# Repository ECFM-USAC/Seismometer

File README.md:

# Seismometer
Seismometer based on a high sensitivity geophone developed with a 24-bit delta-sigma ADC and ESP32 microcontroller.

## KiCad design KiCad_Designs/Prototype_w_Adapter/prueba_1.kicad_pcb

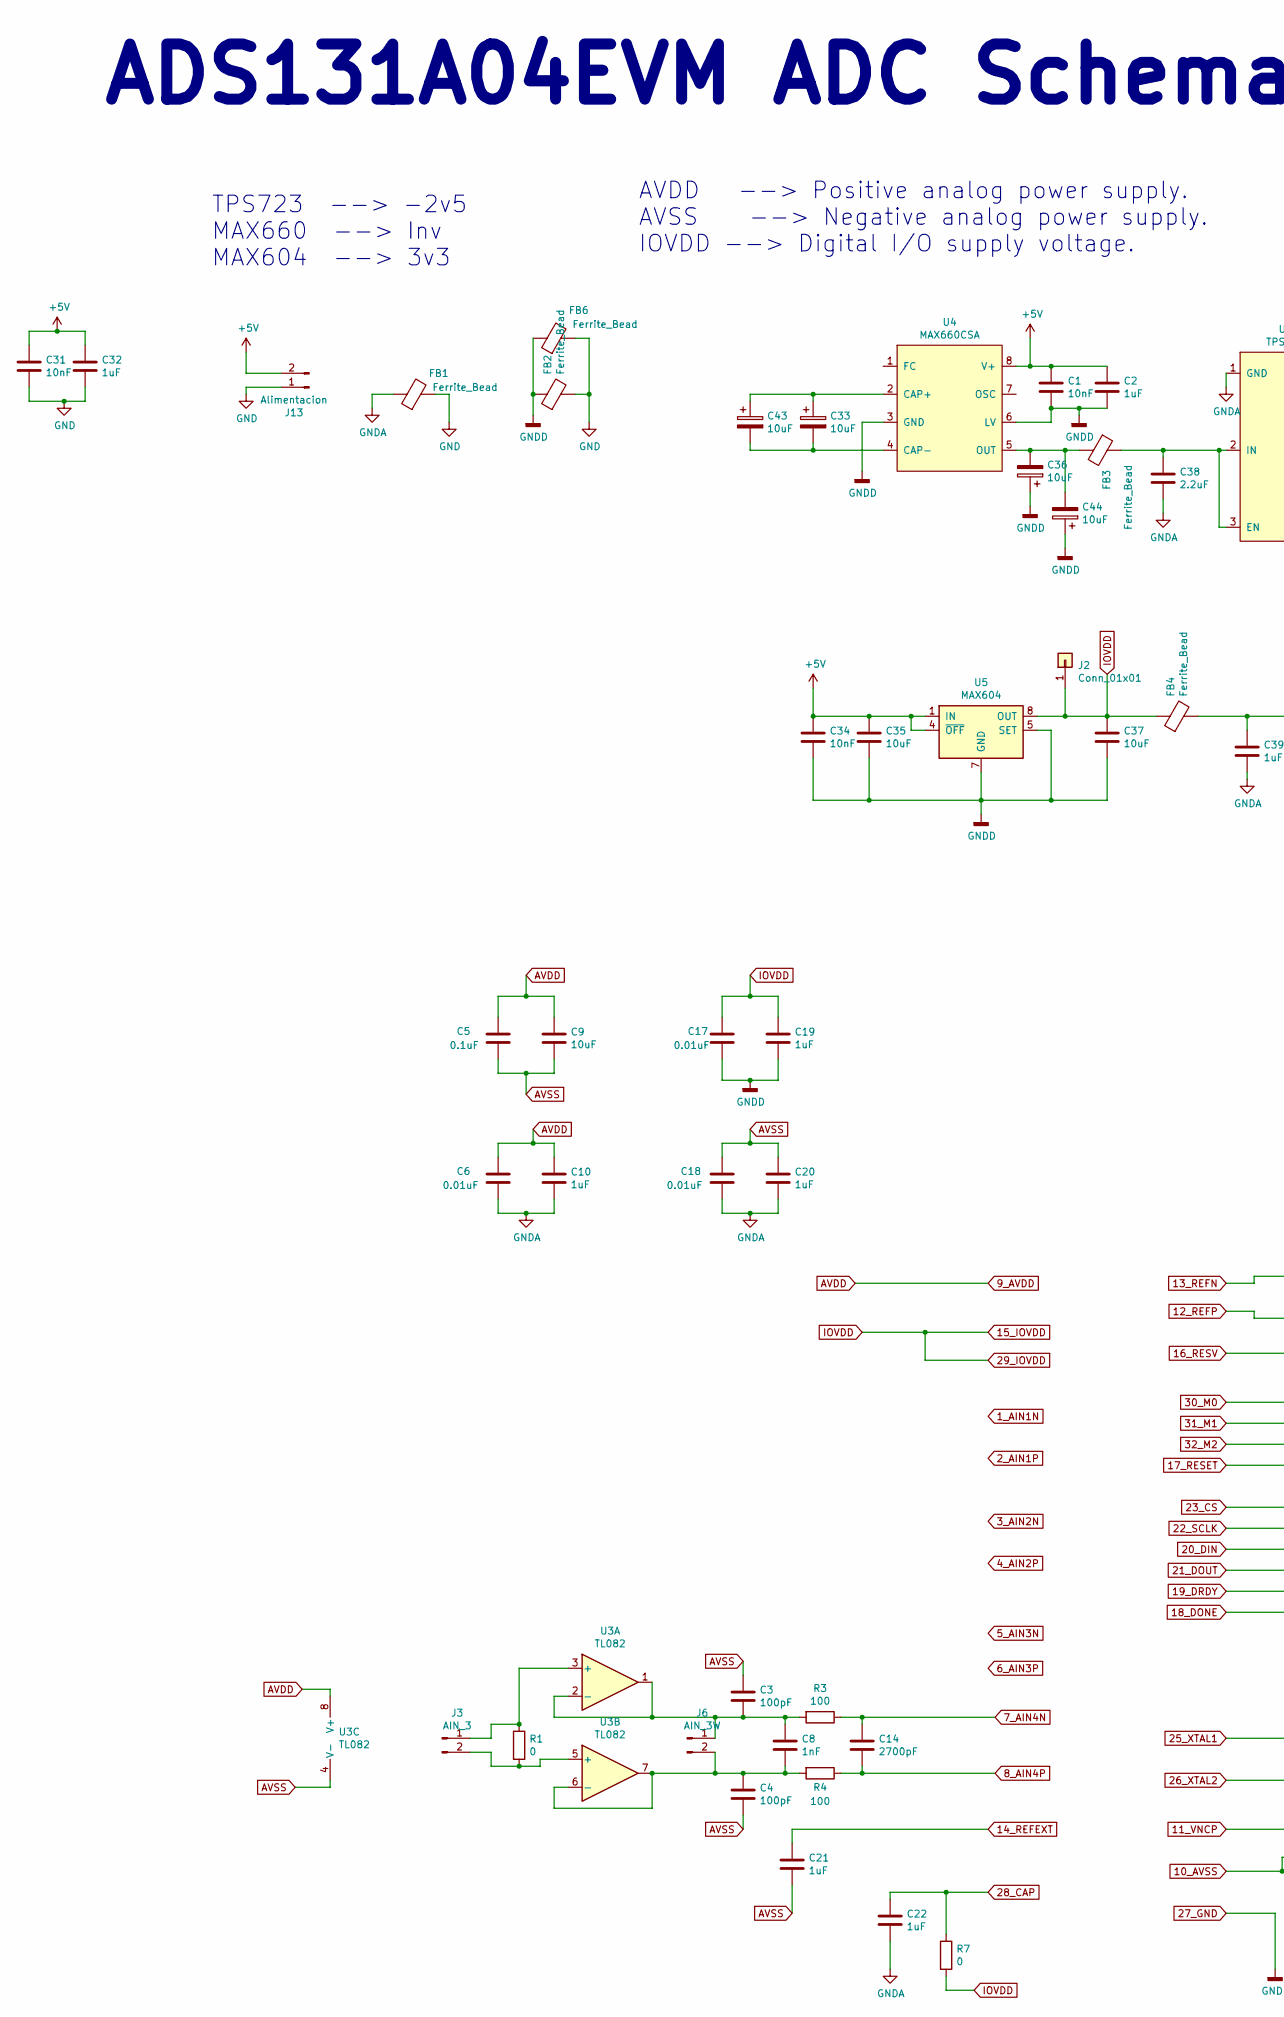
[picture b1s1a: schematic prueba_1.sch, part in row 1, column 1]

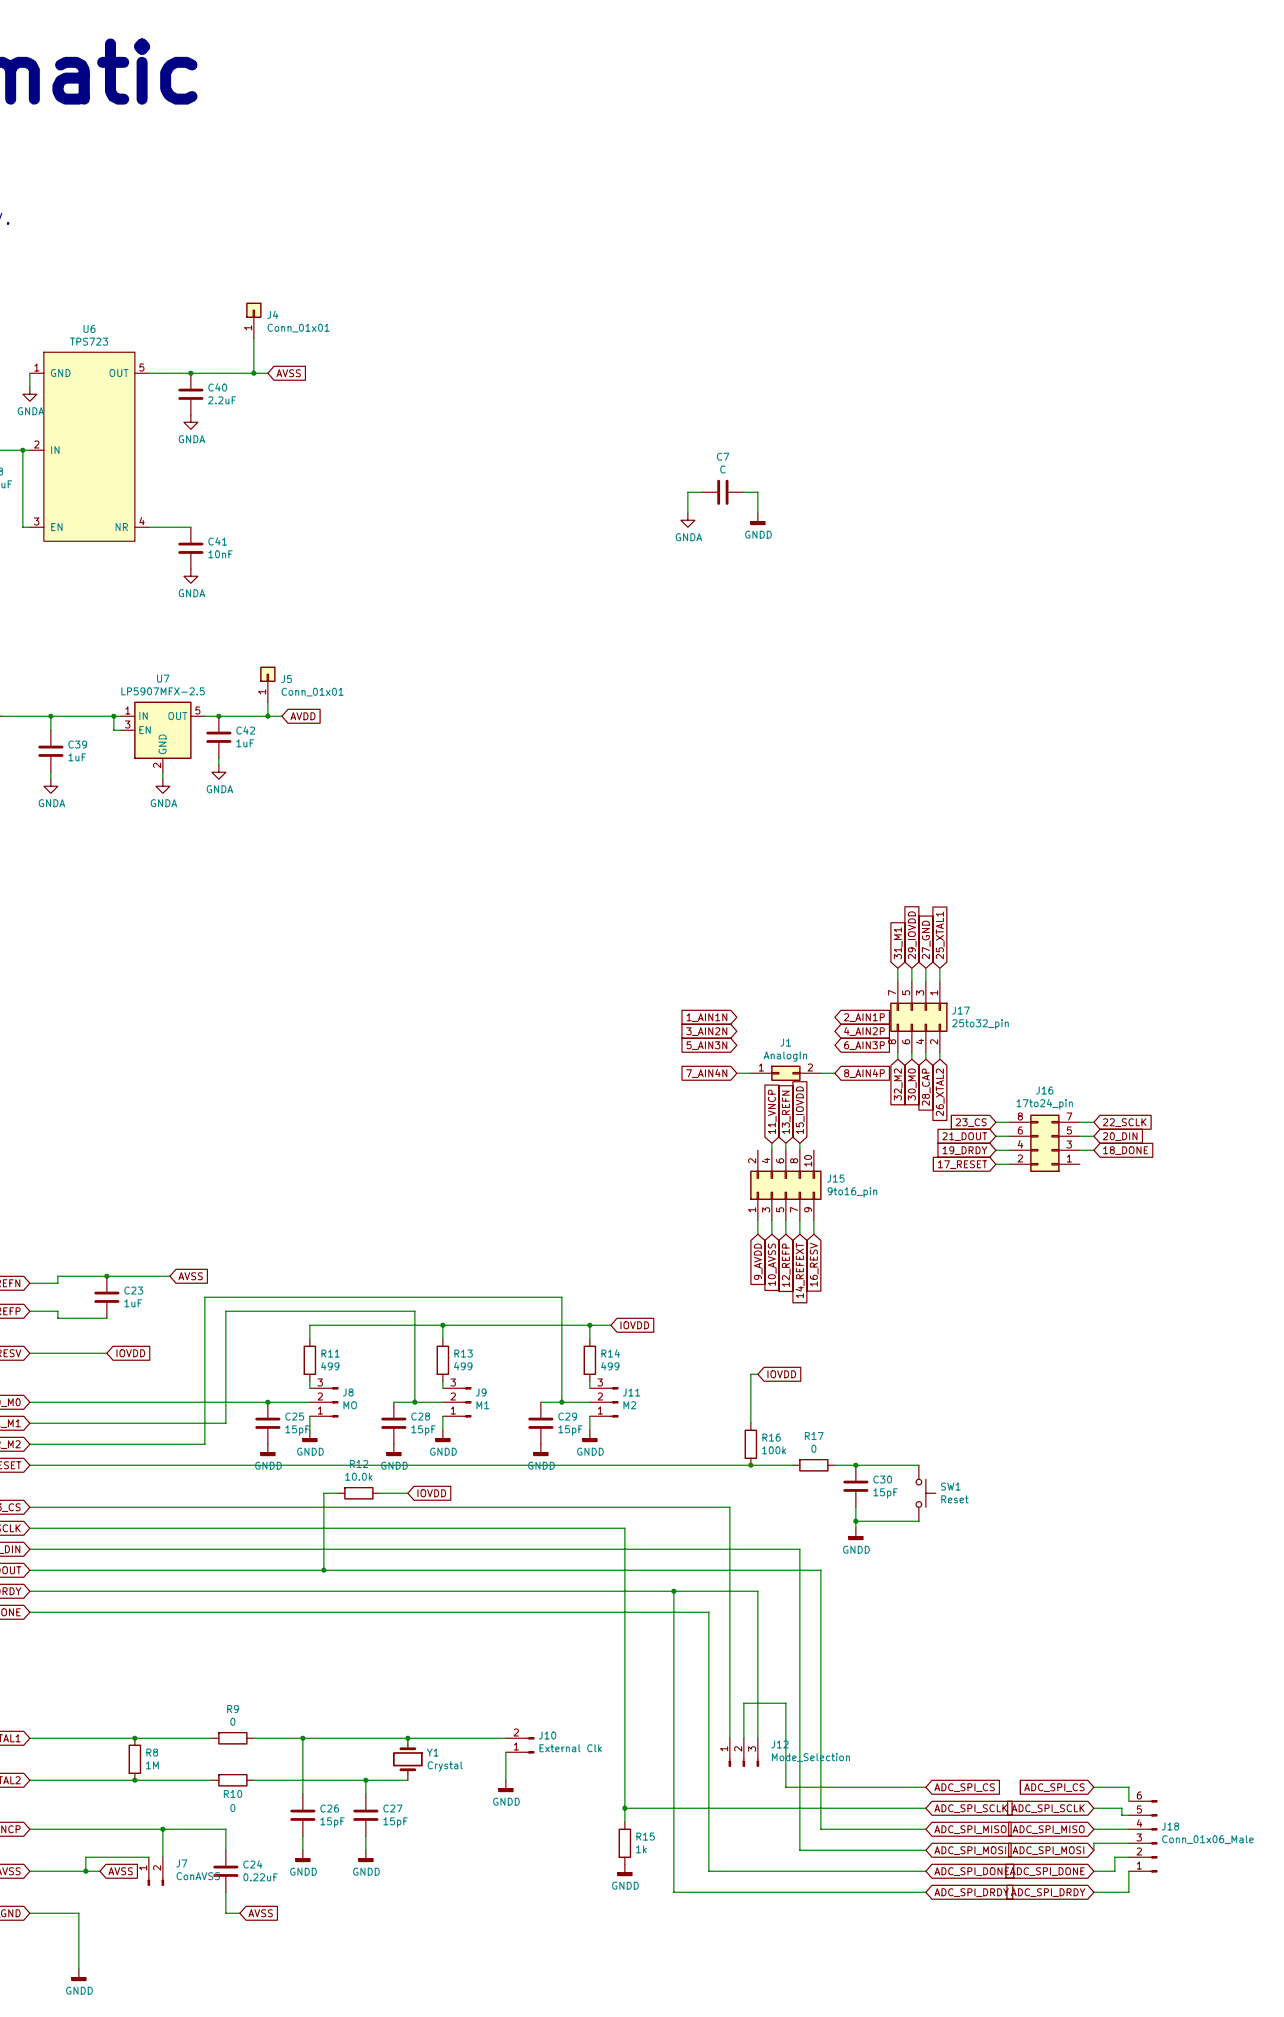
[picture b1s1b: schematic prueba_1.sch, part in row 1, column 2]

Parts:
C1, C31, C34: 10nF; C_0805_2012Metric_Pad1.15x1.40mm_HandSolder
C2, C10, C19, C20, C21, C22, C23, C32, C42: 1uF; C_Disc_D3.0mm_W1.6mm_P2.50mm
C3, C4: 100pF; C_0805_2012Metric_Pad1.15x1.40mm_HandSolder
C5: 0.1uF; C_0805_2012Metric_Pad1.15x1.40mm_HandSolder
C6, C17, C18: 0.01uF; C_0805_2012Metric_Pad1.15x1.40mm_HandSolder
C7: C; C_0805_2012Metric_Pad1.15x1.40mm_HandSolder
C8: 1nF; C_0805_2012Metric_Pad1.15x1.40mm_HandSolder
C9, C33, C35, C36, C37, C43, C44: 10uF; C_Disc_D3.0mm_W1.6mm_P2.50mm
C14: 2700pF; C_0805_2012Metric_Pad1.15x1.40mm_HandSolder
C24: 0.22uF; C_0805_2012Metric_Pad1.15x1.40mm_HandSolder
C25, C26, C27, C28, C29, C30: 15pF; C_0805_2012Metric_Pad1.15x1.40mm_HandSolder
C38, C40: 2.2uF; C_Disc_D3.0mm_W1.6mm_P2.50mm
C39: 1uF; C_0805_2012Metric_Pad1.15x1.40mm_HandSolder
C41: 10nF; C_Disc_D3.0mm_W1.6mm_P2.50mm
FB1, FB2, FB3, FB4, FB6: Ferrite_Bead; L_0805_2012Metric_Pad1.15x1.40mm_HandSolder
J1: AnalogIn; PinHeader_1x02_P2.54mm_Vertical
J2, J4, J5: Conn_01x01; PinHeader_1x01_P2.54mm_Vertical
J3: AIN_3; TerminalBlock_bornier-2_P5.08mm
J6: AIN_3W; PinHeader_1x02_P2.54mm_Vertical
J7: ConAVSS; PinHeader_1x02_P2.54mm_Vertical
J8: MO; PinHeader_1x03_P2.54mm_Vertical
J9: M1; PinHeader_1x03_P2.54mm_Vertical
J10: External Clk; PinHeader_1x02_P2.54mm_Vertical
J11: M2; PinHeader_1x03_P2.54mm_Vertical
J12: Mode_Selection; PinHeader_1x03_P2.54mm_Vertical
J13: Alimentacion; TerminalBlock_bornier-2_P5.08mm
J15: 9to16_pin; PinHeader_2x05_P2.54mm_Vertical
J16: 17to24_pin; PinHeader_2x04_P2.54mm_Vertical
J17: 25to32_pin; PinHeader_2x04_P2.54mm_Vertical
J18: Conn_01x06_Male; PinHeader_1x06_P2.54mm_Vertical
R1, R7, R9, R10, R17: 0; R_0805_2012Metric_Pad1.15x1.40mm_HandSolder
R3, R4: 100; R_0805_2012Metric_Pad1.15x1.40mm_HandSolder
R8: 1M; R_0805_2012Metric_Pad1.15x1.40mm_HandSolder
R11, R13, R14: 499; R_0805_2012Metric_Pad1.15x1.40mm_HandSolder
R12: 10.0k; R_0805_2012Metric_Pad1.15x1.40mm_HandSolder
R15: 1k; R_0805_2012Metric_Pad1.15x1.40mm_HandSolder
R16: 100k; R_0805_2012Metric_Pad1.15x1.40mm_HandSolder
SW1: Reset; SW_DIP_SPSTx01_Slide_6.7x4.1mm_W8.61mm_P2.54mm_LowProfile
U3: TL082; DIP-8_W7.62mm_LongPads
U4: MAX660CSA; DIP-8_W7.62mm_LongPads
U5: MAX604; DIP-8_W7.62mm_LongPads
U6: TPS723; TSOP-5_1.65x3.05mm_P0.95mm
U7: LP5907MFX-2.5; SOT-23-5
Y1: Crystal; Crystal_HC18-U_Vertical

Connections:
7_AIN4N: C14.1, J1.1, R3.1
8_AIN4P: C14.2, J1.2, R4.1
9_AVDD: C5.1, C6.1, C9.1, C10.1, C42.1, J5.1, J15.1, U3.8 (V+), U7.5 (OUT)
10_AVSS: C3.1, C4.2, C5.2, C9.2, C18.1, C20.1, C21.2, C23.1, C24.2, C40.1, J4.1, J7.1, J15.3, J15.6, U3.4 (V-), U6.5 (OUT)
11_VNCP: C24.1, J7.2, J15.4
12_REFP: C23.2, J15.5
14_REFEXT: C21.1, J15.7
15_IOVDD: C17.1, C19.1, C37.1, FB4.1, J2.1, J15.8, J15.9, J17.5, R7.2, R11.1, R12.1, R13.1, R14.1, R16.1, U5.8 (OUT)
17_RESET: J16.2, R16.2, R17.2
18_DONE: J16.3, J18.2
19_DRDY: J12.3, J16.4, J18.1
20_DIN: J16.5, J18.3
21_DOUT: J16.6, J18.4, R12.2
22_SCLK: J16.7, J18.5, R15.1
23_CS: J12.1, J16.8
25_XTAL1: J17.1, R8.1, R9.2
26_XTAL2: J17.2, R8.2, R10.2
27_GND: C1.2, C2.2, C7.1, C17.2, C19.2, C25.2, C26.2, C27.2, C28.2, C29.2, C30.2, C34.2, C35.2, C36.1, C37.2, C44.1, FB2.1, FB6.1, J8.1, J9.1, J10.1, J11.1, J17.3, R15.2, SW1.2, U4.3 (GND), U4.6 (LV), U5.2 (GND), U5.3 (GND), U5.5 (SET), U5.6 (GND), U5.7 (GND)
28_CAP: C22.1, J17.4, R7.1
30_M0: C25.1, J8.2, J17.6
31_M1: C28.1, J9.2, J17.7
32_M2: C29.1, J11.2, J17.8
+5V: C1.1, C2.1, C31.1, C32.1, C34.1, C35.1, J13.2, U4.8 (V+), U5.1 (IN), U5.4 (~OFF)
ADC_SPI_CS: J12.2, J18.6
GND: C31.2, C32.2, FB1.2, FB2.2, FB6.2, J13.1
GNDA: C6.2, C7.2, C10.2, C18.2, C20.2, C22.2, C38.2, C39.1, C40.2, C41.2, C42.2, FB1.1, U6.1 (GND), U7.2 (GND)
unnamed: C3.2, C8.1, J6.1, R3.2, U3.1, U3.2 (-)
unnamed: C4.1, C8.2, J6.2, R4.2, U3.6 (-), U3.7
unnamed: C26.1, J10.2, R9.1, Y1.1
unnamed: C27.1, R10.1, Y1.2
unnamed: C30.1, R17.1, SW1.1
unnamed: C33.1, C43.1, U4.2 (CAP+)
unnamed: C33.2, C43.2, U4.4 (CAP-)
unnamed: C36.2, C44.2, FB3.2, U4.5 (OUT)
unnamed: C38.1, FB3.1, U6.2 (IN), U6.3 (EN)
unnamed: C39.2, FB4.2, U7.1 (IN), U7.3 (EN)
unnamed: C41.1, U6.4 (NR)
unnamed: J3.1, R1.1, U3.3 (+)
unnamed: J3.2, R1.2, U3.5 (+)
unnamed: J8.3, R11.2
unnamed: J9.3, R13.2
unnamed: J11.3, R14.2

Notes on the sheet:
ADS131A04EVM ADC Schematic
AVDD --> Positive analog power supply. AVSS --> Negative analog power supply. IOVDD --> Digital I/O supply voltage.
TPS723 --> -2v5 MAX660 --> Inv MAX604 --> 3v3

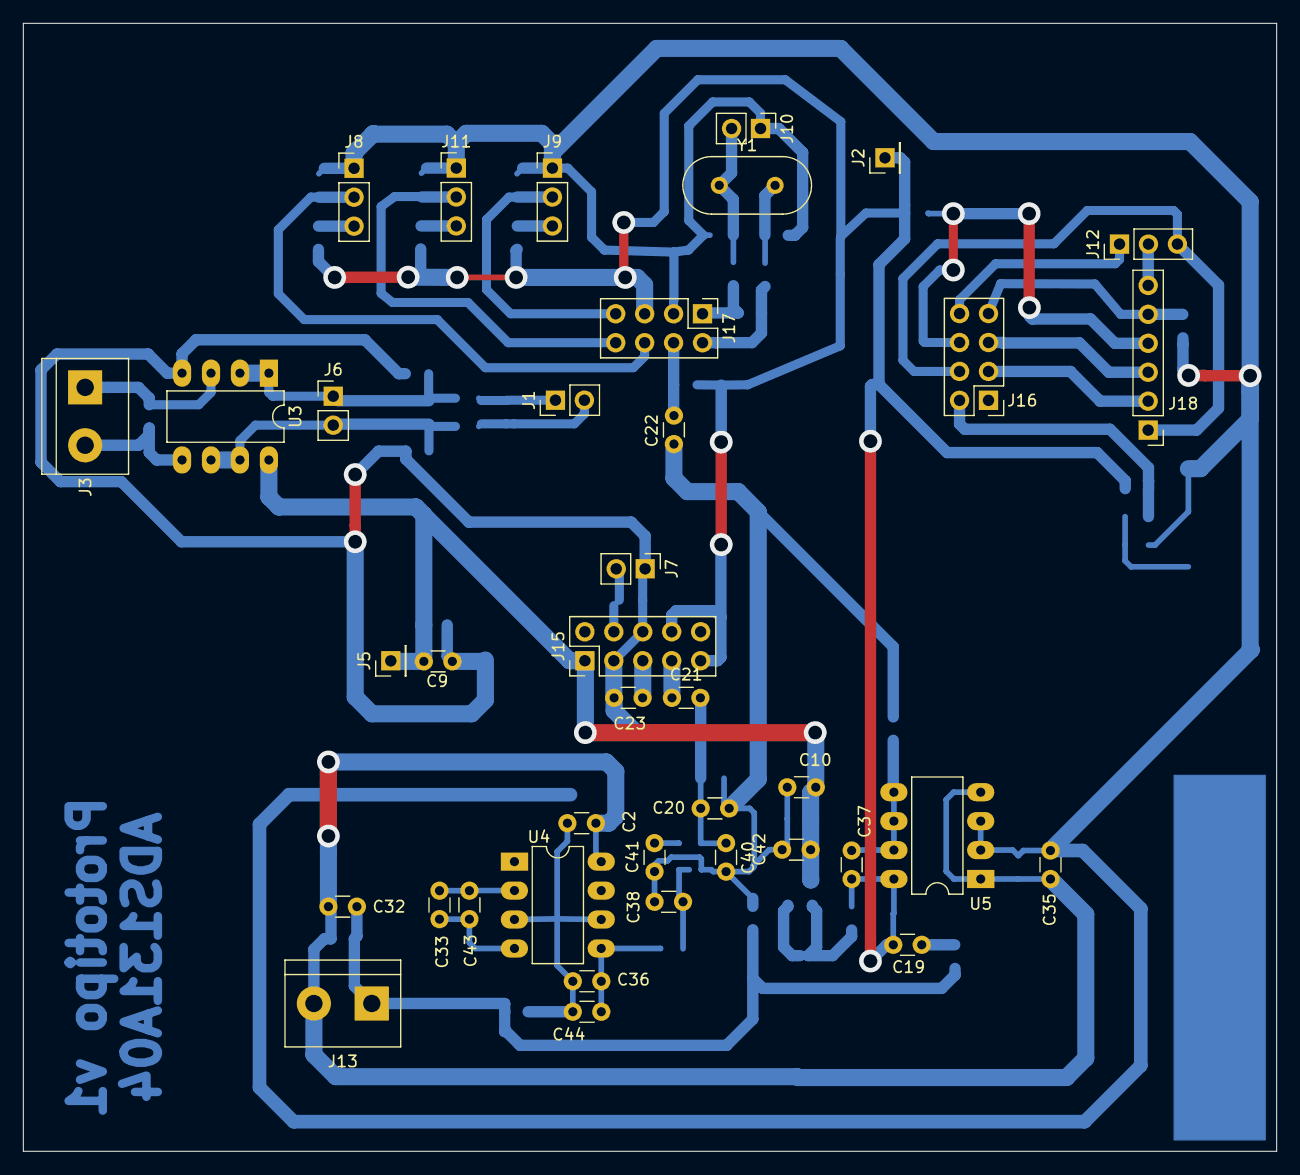
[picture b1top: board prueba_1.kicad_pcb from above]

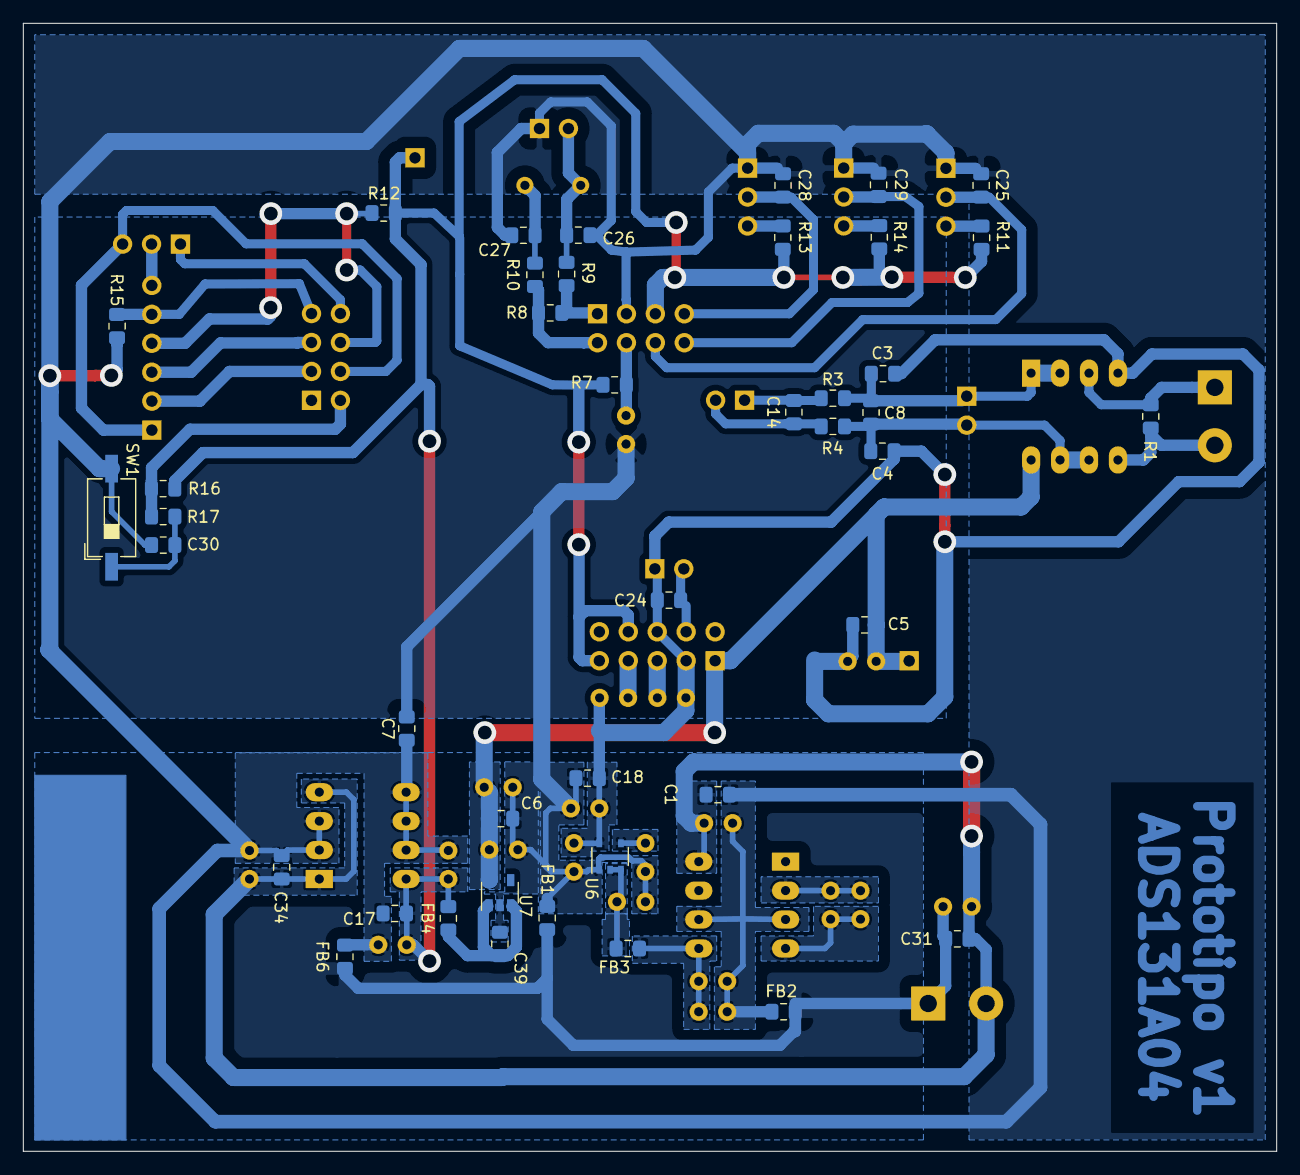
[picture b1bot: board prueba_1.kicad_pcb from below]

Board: 2 copper layers, 110.0 x 99.0 mm, 81 parts (42 on the bottom side), 42 nets.

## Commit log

2020-04-30 First Version
2020-05-04 Prototype Schematic Updated
